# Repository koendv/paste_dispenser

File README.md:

# Solder Paste Dispenser

This is a solder paste dispenser. The controller supports unipolar and bipolar stepper motors, a foot pedal switch, an OLED display, a LED that blinks faster when the motor runs faster, and a menu system. The board has been designed with easy soldering in mind, using components size 0805 and up.

## Foot switch

Dispensing can be initiated either by pressing the *push* button on the dispenser, or by pushing down a foot pedal switch.

A foot pedal switch has the advantage that it frees up a hand. Using a foot switch is also more stable; pushing a button on the solder dispenser always moves the syringe tip a little bit.

Suitable foot pedals are [Adafruit product ID 423](https://www.adafruit.com/product/423) and [Sparkfun COM-11192](https://www.sparkfun.com/products/11192), and their equivalents at ebay and aliexpress.

These foot pedal switches are simple on/off switches, normally open. Speed controller foot pedals with a potentiometer will **not** work.

## Display

The display shows the motor speed.

The OLED display is a generic OLED module 0.91" diagonal, 128x32 pixel, I2C, SSD1306, as found on ebay, aliexpress and [others](https://www.google.com/search?q=OLED+module+0.91%22+128x32+I2C+SSD1306+price). Before buying, check the module has a 4-pin connection - GND, VCC, SDA, SCK - and uses a SSD1306 controller. The display *ought* not to touch any of the components below, but you can always put a bit of Kaptan tape on the back of the display, just to make sure.

The OLED display is optional. If you choose not to install the OLED display you can still check stepper speed on the serial console.

## Menu

There is a settings menu on the serial port. The serial port runs at 115200, 8N1, no flow control. Access the menu using a vt100 ansi terminal emulation, e.g. [PuTTY](https://putty.org/) on Windows, or *minicom* on Linux. On Android, use an USB OTG adapter and *Serial USB Terminal*. The settings menu allows you to configure forward speed, backward speed, pullback, and microstepping, and to store and recall these settings from non-volatile memory. The menu looks like this:

	[f] Forward speed 125 steps/sec
	[s] Forward steps 0 steps
	[b] Backward speed 500 steps/sec
	[d] Pullback delay 2000 millisec
	[p] Pullback steps 0 steps
	[m] Microstepping 2
	[n] Profile number 0
	[r] Restore profile
	[w] Save profile
	[h] Help

### Speed
Forward speed can be set using the *faster*/*slower* buttons on the dispenser itself or using the console menu.

If *forward steps* is zero, the syringe plunger is pushed down as long as you press the *push* button or the foot switch pedal. This is useful for making beads, and the normal setting when dispensing solder paste. If *forward steps* is non-zero, pushing the *forward* button or the foot switch moves the plunger down exactly the number of steps in the settings. This is useful for making precise, repeatable dots, e.g. as a glue or lubricating oil dispenser.

Backward speed can only be set using the console menu.

### Pullback
Sometimes liquid keeps oozing out after you stop dispensing. If *pullback steps* is non-zero, then after a *pullback delay* period of inactivity the plunger will move back *pullback steps*, to stop liquid oozing out. How successful this is and how many steps the plunger needs to pull back to stop the oozing depends upon the viscosity of the liquid. *Pullback* works better with low viscosity liquids than with high viscosity paste. Pullback is interesting if you use this as a dispenser for e.g. cyanoacrylate glue.

### Microstepping
The controller supports up to 1/64 microstepping. This is open loop voltage control microstepping.
Choose speed and microstepping that goes well with your stepper motor. This may take a bit of trial and error. Default is half-stepping, suitable for 28BYJ-48 steppers .

### Saved Profiles

Once you have found a setting that works, you can save it for later. Up to five profiles can be saved. These profiles are remembered even when the power is turned off. After power-up the last saved settings are used.

## Power supply

If you want to play it safe, use a 5.0V 1A phone charger as power supply. The TB6612 stepper motor driver IC supports 5V 1.2A continuous, but can be damaged by higher currents. Using a power supply with a maximum current less than 1.2A protects the driver IC in case of short circuit or stall.

The voltage range is 4.5V to 5.5V. More than 5.5V is too much for the atmega328p microcontroller; less than 4.5V and the TB6612 stepper driver stops working.

The board has a MOSFET for reverse polarity protection.

## Connecting everything

The controller board has four headers:

* J1 is the ISP connector for downloading the initial firmware to the atmega microcontroller.
* J2 connects to an USB to serial adapter (pins +5V, RX, TX, GND) and the footswitch (pins FTSW, GND). The footswitch is optional, but very handy.
* J3 is the connector for the stepper motor. Both unipolar and bipolar steppers can be connected. Connect one coil to pins A1 and A2, and one coil to pins B1 and B2. Connect the center tap of unipolar steppers to pin GND.
* J4 is the connector for the optional OLED display. Solder a 4-position female Dupont housing here.

## Bootstrapping

The first compile is the hardest.

Open the Arduino IDE. Compile the *paste dispenser* sketch, with these settings:

* Board: Arduino Pro or Pro Mini,
* Processor: Atmega328P (5V, 16MHz).

Generate an Intel Hex file with _Sketch -> Export Compiled Binary_. This creates two .hex files in the project directory, `arduino.ino.eightanaloginputs.hex` and `arduino.ino.with_bootloader.eightanaloginputs.hex`. The hex file we need is the one with the bootloader.
The ISP programmer is an arduino with the same logic levels as the target system. As the solder paste dispenser uses 5V logic, we need an Arduino with 5V logic levels as ISP programmer. Connect a 5V Arduino, e.g. an Arduino Uno, to your system. Compile and upload the _File -> Examples -> ArduinoISP_ sketch to the Uno. Connect the Arduino Uno to the solder paste dispenser board as follows:

Signal|Uno    |ISP pin
------|-------|--------
RST	|Uno pin 10|5
MOSI|Uno pin 11|4
MISO|Uno pin 12|1
SCK|Uno pin 13|3
VCC|Uno 5V|2
GND|Uno GND|6

Find `avrdude` in your Arduino IDE directories, change to the appropriate directory and do the following incantation:

	koen@raspberrypi:/opt/arduino-1.8.9/hardware/tools/avr $ ./bin/avrdude -C ./etc/avrdude.conf -p m328p -P /dev/ttyACM0 -c avrisp -b 19200 -U flash:w:/home/koen/src/paste_injector/arduino/arduino.ino.with_bootloader.eightanaloginputs.hex

where `/dev/ttyACM0` is the usb port of your Arduino Uno. Flashing should take about 20 seconds, and ends with "`xxx bytes of flash verified`" and "`Fuses OK`".

Set the fuses of the atmega328p for an external resonator at 16MHz:

	koen@raspberrypi:/opt/arduino-1.8.9/hardware/tools/avr $ ./bin/avrdude -C ./etc/avrdude.conf -c avrisp -p m328p -P /dev/ttyACM0 -b 19200  -U lfuse:w:0xff:m -U hfuse:w:0xda:m -U efuse:w:0xfd:m

The avrdude output ought to say: ```avrdude: safemode: Fuses OK (E:FD, H:DA, L:FF)```

If you just want to read the fuses:

	koen@raspberrypi:/opt/arduino-1.8.9/hardware/tools/avr $  ./bin/avrdude -C ./etc/avrdude.conf -c avrisp -p m328p -P /dev/ttyACM0 -b 19200 -U lfuse:r:-:i -v

This finishes writing bootloader and sketch to the solder paste dispenser. Disconnect the Arduino Uno. The atmega328p now contains a bootloader. Sketches can now be uploaded using the solder paste dispenser serial port.

## Firmware

The solder paste dispenser is an arduino system. Once the bootstrap loader has been installed the solder paste dispenser can be programmed using the arduino IDE.

To avoids spurious resets when connecting to the serial port, there is no capacitor between DTR and reset. But this also means that if you want to develop firmware for this board there is no automatic reset before uploading. Three options:

* Upload firmware using the ISP connector. This has to be done at least once, to upload the bootloader.
* Use the serial port to upload. This is what I usually do. Before uploading connect RST and ground with a Dupont jumper wire. RST and ground are next to each other on the ISP connector. In the Arduino IDE, click Sketch -> Upload, count to three and remove the jumper wire.
* When developing connect a 100n capacitor between serial adapter DTR and ISP connector RST pin. This allows the IDE to reset the microcontroller automatically just before uploading using the serial port.

## Soldering your own

The github contains arduino source and kicad pcb design files. You'll find the [schematic](https://github.com/koendv/paste_dispenser/raw/master/kicad/paste_dispenser/paste_dispenser_schematic.pdf), the [board layout](https://github.com/koendv/paste_dispenser/raw/master/kicad/paste_dispenser/paste_dispenser_board.pdf), and the [bill of materials](https://github.com/koendv/paste_dispenser/blob/master/kicad/paste_dispenser/paste_dispenser.csv). This is a link to the pcb as an orderable [shared project at oshpark](http://www.oshpark.com/shared_projects/V5txbi41), and these are the components as a [shared project at Mouser](https://www.mouser.com/ProjectManager/ProjectDetail.aspx?AccessID=61ff8d7d43). Here are [zipped gerbers](https://github.com/koendv/paste_dispenser/raw/master/kicad/paste_dispenser/gerbers.zip) for pcb manufacturing at [jlcpcb](https://jlcpcb.com/).

If you prefer not to solder SMD's you can also build the controller on a breadboard or as a through-hole pcb, as in this [fritzing sketch](https://github.com/koendv/paste_dispenser/raw/master/fritzing/paste_dispenser_fritzing_breadboard.pdf) of a 5V 16MHz Arduino Pro Mini and a TB6612 breakout module.

## Printing your own

Leave part orientation as is when imported into PrusaSlicer. Designed to print without support.

The [openscad/](https://github.com/koendv/paste_dispenser/tree/master/openscad) directory contains the .stl files for [3d-printing](https://www.treatstock.com/c/seaside-3d) the mechanical part of the solder paste dispenser in ABS using FDM. These parts need finishing as follows:

* Take the workpiece [insert_practice](https://github.com/koendv/paste_dispenser/blob/master/openscad/aerzetix-C19143/insert_practice.stl) and place 4 heat-set inserts, as a test. Set your soldering iron to the filament extrusion temperature used during 3D printing, about 255&deg;C.
* Take the workpiece [motor_mount](https://github.com/koendv/paste_dispenser/blob/master/openscad/aerzetix-C19143/motor_mount.stl) and place 4 heat-set inserts.
* Take the workpiece [plunger](https://github.com/koendv/paste_dispenser/blob/master/openscad/aerzetix-C19143/plunger.stl) and place 1 heat-set insert.
* Using **a drop** of acetone, glue the small conical [plunger tip](https://github.com/koendv/paste_dispenser/blob/master/openscad/aerzetix-C19143/plunger_tip.stl) to the plunger. Acetone is a solvent for ABS.

Mechanical assembly is next.
## Assembly

The mechanical part consists of stepper motor, coupler and leadscrew. 

The stepper motor is a [28BYJ-48](https://www.adafruit.com/product/858). The motor can be used "as is", or [modified to bipolar](https://coeleveld.com/wp-content/uploads/2016/10/Modifying-a-28BYJ-48-step-motor-from-unipolar-to-bipolar.pdf) for additional torque.

The leadscrew is 64mm of M4 threaded rod, 0.7mm pitch. The leadscrew mates with the M4 threaded insert in the plunger.

The coupler between motor and leadscrew is an [Aluminum 4mm to 5mm shaft couplers](https://www.google.com/search?&q=%2B%22D19*L25%22+Shaft+Coupling+Aluminium+flexible+%2B%224x5%22+aliexpress), readily available from ebay or aliexpress. The all-metal construction easily handles the torque.

Attach the stepper motor to the motor mount using two nylon or stainless steel M4x10 hex socket screws. Nylon screws keep the weight down. Attach the [syringe holder](https://github.com/koendv/paste_dispenser/blob/master/openscad/aerzetix-C19143/syringe_holder.stl) to the motor block with two M4x10 hex socket screws.

The syringe used is a BD 10cc "Luer-Lok", or one of its many [oriental clones](https://www.google.com/search?q=10cc+syringe+smt+smd+site%3A.aliexpress.com). Remove the black rubber piston head from the syringe and put it on the solder paste dispenser plunger.

Friction between rubber piston and syringe is what keeps the plunger from spinning. If during operation the plunger rotates instead of moving forward, clean the sides of the black rubber piston head with (isopropyl) alcohol to remove any grease. 

## Adding the Electronics

Align the pins of the PCB with the holes in the front of the motor mount. Fix the PCB in place with adhesive Velcro tape. Plug the OLED display in the connector marked "SDA SCK VCC GND". Connect the stepper motor to header J3.

Run 1-2m of cable from the 6-pin Dupont connector on the right of the PCB. The cable connects solder paste dispenser to a [5V TTL serial to USB converter](https://www.google.com/search?q=CH340C+site%3A.aliexpress.com) (pins +5V,RX,TX,GND) and the foot switch (pins FTSW, GND). 

If the motor turns the wrong way, swap pins A1 and A2, or pins B1 and B2.

At this point you have a working solder paste dispenser, ready for use.

## Practice makes perfect

For practice fill a syringe with a small amount (approx. 1 ml) of toothpaste. Print a pcb at scale 1:1 in black and white on paper and practice depositing toothpaste until you are comfortable with the solder paste dispenser.

Before filling the syringe, run a nylon wire inside the syringe body. A small piece of fishing line is suitable. This nylon wire creates a small leak in the seal between plunger and syringe body, allowing the air to escape while you push the plunger down. Once the plunger is down, simply pull the nylon wire out and you can begin dispensing.

## Notes

* There are a few situations which may result in breakage.
If the piston pushes against the bottom of an empty syringe, something has to give.
Likewise, if you try to squeeze paste out of a stoppered syringe.
In general, avoid "unstoppable force meets inmovable object" situations. Something will break - the motor may tear itself off its mounts, for instance.

* When not in use, loosen the syringe holder screws so the syringe isn't under constant pressure.

* A solder paste dispenser is a small motor which pushes the plunger of a syringe. You can use it for solder paste or solder flux, but the dispenser can also be used as a syringe pump, to create small dots of glue in a precise and repeatable way, or to put small drops of lubricating oil on a mechanism.

* The controller is not restricted to any specific model of solder paste dispenser; if a syringe pump uses a 5- or 6-wire unipolar or a 4-wire bipolar stepper motor, there's a reasonable chance this will work. Just check the stepper works at 5V and current stays below 1.2 amps.

* FDM print settings: Increase perimeters on the pieces with heat-set inserts ([motor_mount](https://github.com/koendv/paste_dispenser/blob/master/openscad/aerzetix-C19143/motor_mount.stl) and [plunger](https://github.com/koendv/paste_dispenser/blob/master/openscad/aerzetix-C19143/plunger.stl)); this gives the heat-set inserts more material to grip onto. 

* Exactly how hard do we need to push? Take a syringe and (kitchen) scales. Grab the syringe by the syringe body, and push the syringe piston against the scales until the syringe releases solder paste. Take note of the weight the scales indicate. If the scales indicates pounds, multiply by 5 to get Newtons. If the scales indicate kilogrammes, multiply by 10 to get Newtons.
Measured this way, pushing the plunger of 5cc and 10cc syringes of solder flux and solder paste needs a force between 20N and 30N.

* The kicad pcb hardware design is under Creative Commons - Attribution Share Alike license.

* This design was inspired by solder paste dispensers by [zapta](https://www.thingiverse.com/thing:1119914) and [geir](https://www.thingiverse.com/thing:384680). The mechanical part is a remix of zapta's, with only minor changes.

* This design was built around a Atmega328p "Pro Mini" and a TB6612 stepper driver. An alternative design would be a STM32F103 "Black Pill" and a TMC2130 SilentStepStick stepper driver. The STM32F103 has enough cpu to run a comprehensive menu system and built-in usb. The TMC2130 stall detection allows detecting when the plunger has reached the bottom of the syringe, so software can move the plunger back a few steps before any mechanical damage occurs. But such a design would hit a different price point.

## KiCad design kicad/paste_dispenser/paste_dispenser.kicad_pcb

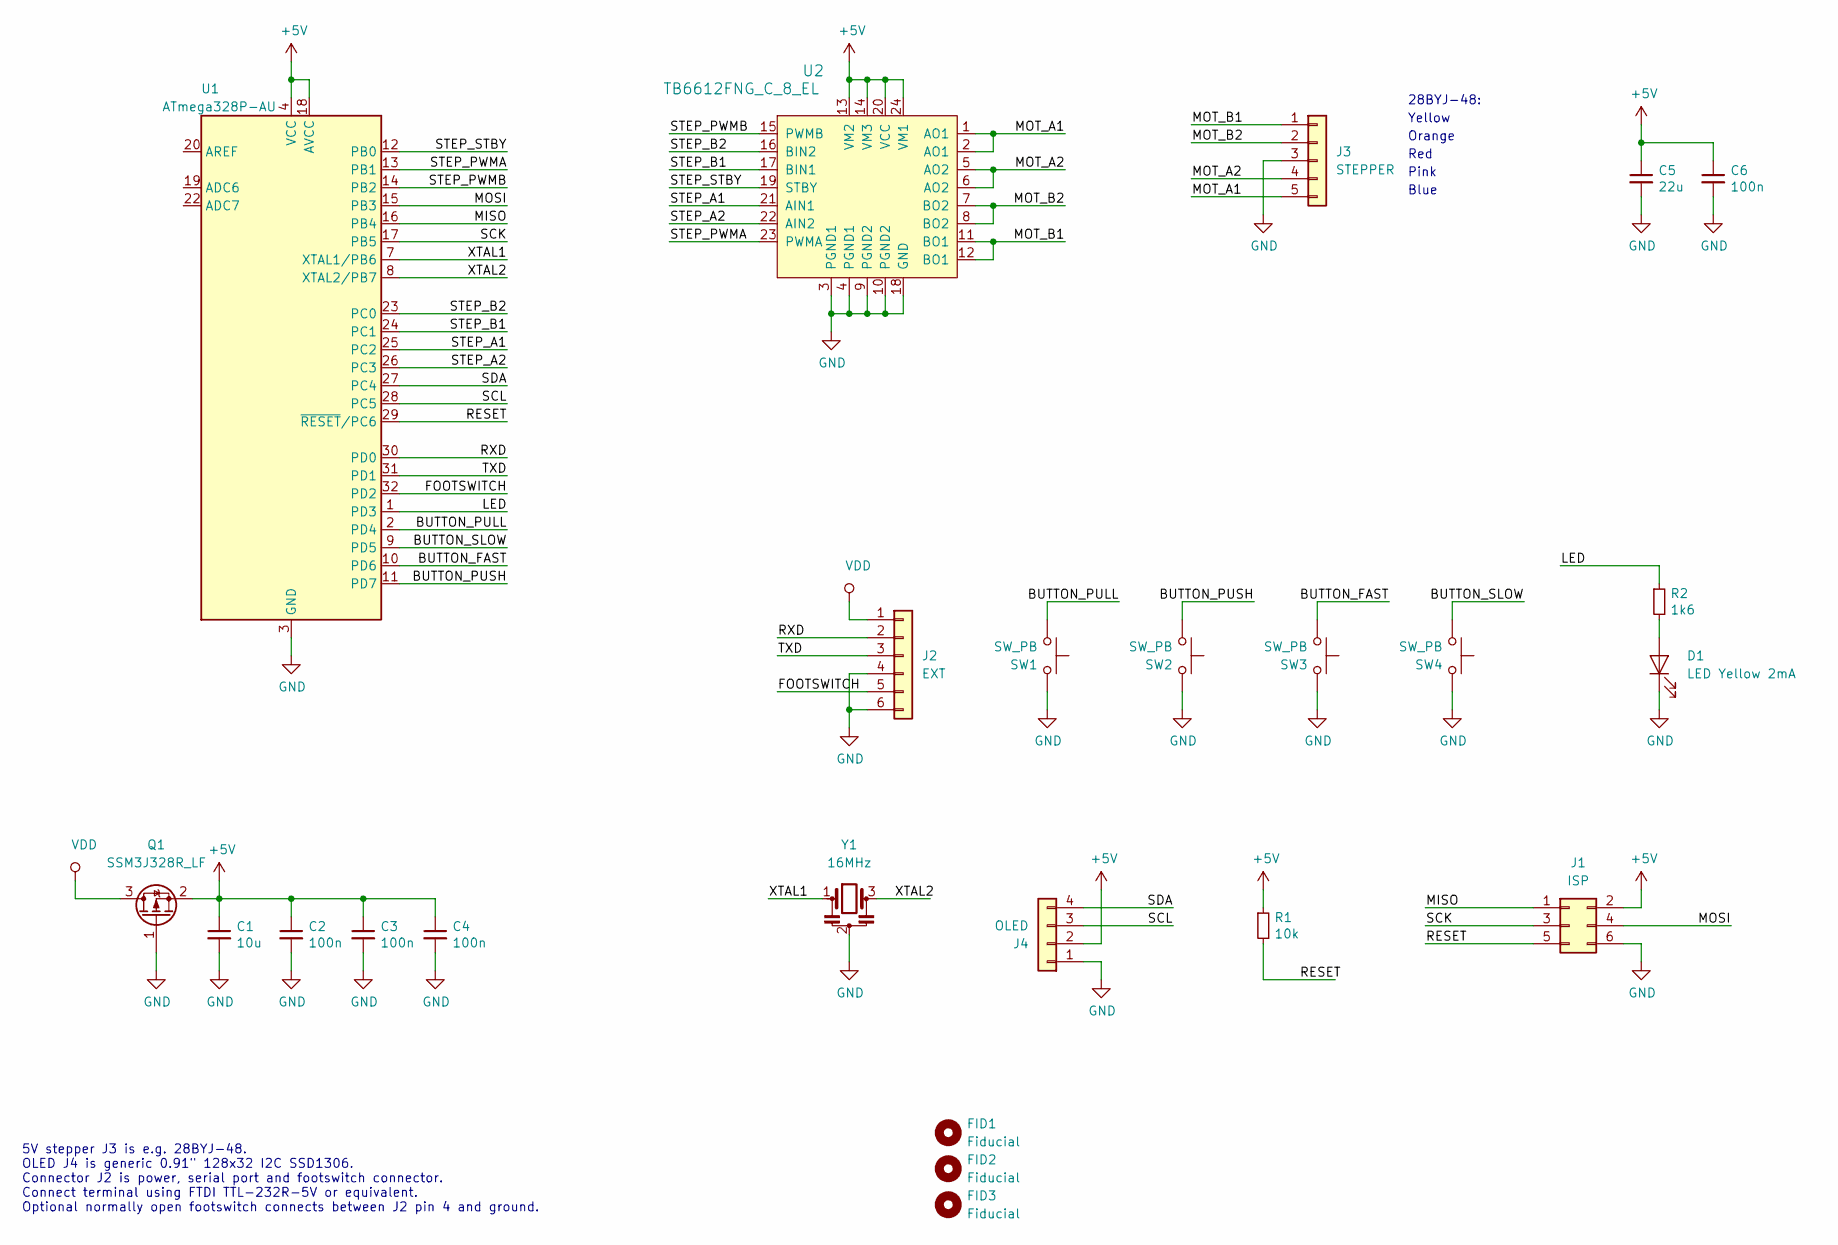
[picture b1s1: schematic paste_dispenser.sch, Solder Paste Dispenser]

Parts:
C1: 10u; C_0805_2012Metric; Manufacturer Part No CC805KKX5R7BB106
C2, C3, C4, C6: 100n; C_0805_2012Metric; Manufacturer Part No CC805KRX7R7BB104
C5: 22u; C_1206_3216Metric; Manufacturer Part No EMK316BB7226ML-T
D1: LED Yellow 2mA; LED_0805_2012Metric; Manufacturer Part No APTD2012LSYCK
FID1, FID2, FID3: Fiducial; Fiducial_1mm_Dia_2.54mm_Outer_CopperTop
J1: ISP; PinHeader_2x03_P2.54mm_Vertical; Manufacturer Part No 2822
J2: EXT; PinHeader_1x06_P2.54mm_Vertical; Manufacturer Part No 70553-0005
J3: STEPPER; PinHeader_1x05_P2.54mm_Vertical; Manufacturer Part No DNP
J4: OLED; PinSocket_1x04_P2.54mm_Vertical; Manufacturer Part No M20-7820442
Q1: SSM3J328R_LF; SOT-23; Manufacturer Part No SSM3J328R,LF
R1: 10k; R_0805_2012Metric; Manufacturer Part No AC0805FR-0710KL
R2: 1k6; R_0805_2012Metric; Manufacturer Part No AC0805FR-071K6L
SW1, SW2, SW3, SW4: SW_PB; SW_PUSH_6mm; Manufacturer Part No B3F-1000
U1: ATmega328P-AU; TQFP-32_7x7mm_P0.8mm; Manufacturer Part No ATMEGA328P-AU
U2: TB6612FNG_C_8_EL; LSSOP-24_W5.6mm; Manufacturer Part No TB6612FNG,C,8,EL
Y1: 16MHz; Resonator_SMD_muRata_CSTxExxV-3Pin_3.0x1.1mm_HandSoldering; Manufacturer Part No CSTNE16M0V530000R

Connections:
+5V: C1.1, C2.1, C3.1, C4.1, C5.1, C6.1, J1.2, J4.2, Q1.2 (S), R1.1, U1.4 (VCC), U1.6 (VCC), U1.18 (AVCC), U2.13 (VM2), U2.14 (VM3), U2.20 (VCC), U2.24 (VM1)
/BUTTON_FAST: SW3.1, U1.10 (PD6)
/BUTTON_PULL: SW1.1, U1.2 (PD4)
/BUTTON_PUSH: SW2.1, U1.11 (PD7)
/BUTTON_SLOW: SW4.1, U1.9 (PD5)
/FOOTSWITCH: J2.5, U1.32 (PD2)
/LED: R2.1, U1.1 (PD3)
/MISO: J1.1, U1.16 (PB4)
/MOSI: J1.4, U1.15 (PB3)
/MOT_A1: J3.5, U2.1 (AO1), U2.2 (AO1)
/MOT_A2: J3.4, U2.5 (AO2), U2.6 (AO2)
/MOT_B1: J3.1, U2.11 (BO1), U2.12 (BO1)
/MOT_B2: J3.2, U2.7 (BO2), U2.8 (BO2)
/RESET: J1.5, R1.2, U1.29 (~RESET~/PC6)
/RXD: J2.2, U1.30 (PD0)
/SCK: J1.3, U1.17 (PB5)
/SCL: J4.3, U1.28 (PC5)
/SDA: J4.4, U1.27 (PC4)
/STEP_A1: U1.25 (PC2), U2.21 (AIN1)
/STEP_A2: U1.26 (PC3), U2.22 (AIN2)
/STEP_B1: U1.24 (PC1), U2.17 (BIN1)
/STEP_B2: U1.23 (PC0), U2.16 (BIN2)
/STEP_PWMA: U1.13 (PB1), U2.23 (PWMA)
/STEP_PWMB: U1.14 (PB2), U2.15 (PWMB)
/STEP_STBY: U1.12 (PB0), U2.19 (STBY)
/TXD: J2.3, U1.31 (PD1)
/XTAL1: U1.7 (XTAL1/PB6), Y1.1
/XTAL2: U1.8 (XTAL2/PB7), Y1.3
GND: C1.2, C2.2, C3.2, C4.2, C5.2, C6.2, D1.1 (K), J1.6, J2.4, J2.6, J3.3, J4.1, Q1.1 (G), SW1.2, SW2.2, SW3.2, SW4.2, U1.3 (GND), U1.5 (GND), U1.21 (GND), U2.3 (PGND1), U2.4 (PGND1), U2.9 (PGND2), U2.10 (PGND2), U2.18 (GND), Y1.2
unnamed: D1.2 (A), R2.2
VDD: J2.1, Q1.3 (D)

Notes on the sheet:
5V stepper J3 is e.g. 28BYJ-48. OLED J4 is generic 0.91" 128x32 I2C SSD1306. Connector J2 is power, serial port and footswitch connector. Connect terminal using FTDI TTL-232R-5V or equivalent. Optional normally open footswitch connects between J2 pin 4 and ground.
Yellow
Orange
Red
Pink
Blue
28BYJ-48:

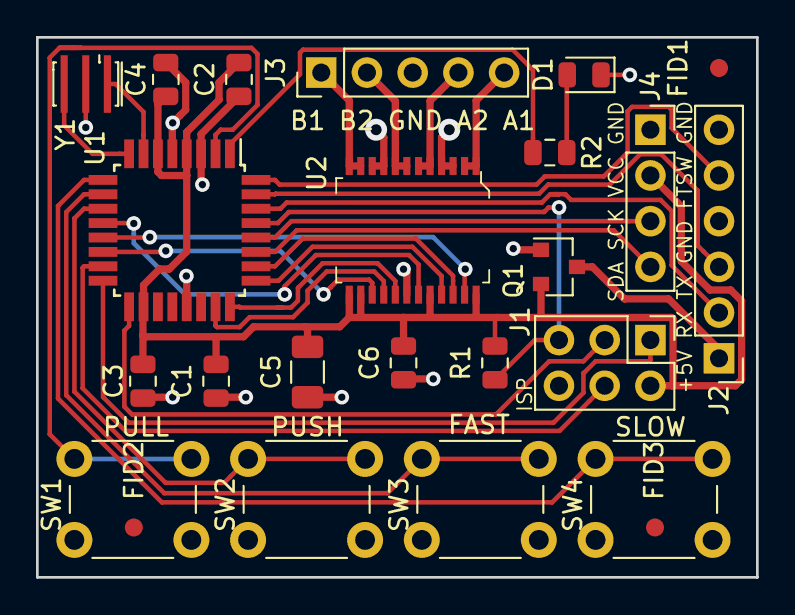
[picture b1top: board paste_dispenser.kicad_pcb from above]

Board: 2 copper layers, 40.0 x 30.0 mm, 24 parts (0 on the bottom side), 31 nets.

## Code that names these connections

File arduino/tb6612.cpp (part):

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
  // bitmasks for the stepper wires.
  
  static const uint8_t AIN1 = (1 << 2); // Coil A+ corresponds to port C bit 2. (PC2)
  static const uint8_t AIN2 = (1 << 3); // Coil A- corresponds to port C bit 3. (PC3)
  static const uint8_t BIN1 = (1 << 1); // Coil B+ corresponds to port C bit 1. (PC1)
  static const uint8_t BIN2 = (1 << 0); // Coil B- corresponds to port C bit 0. (PC0)
  
  static const uint8_t kAllPins = AIN1 | AIN2 | BIN1 | BIN2; // mask for all stepper wires.
  
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
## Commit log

2019-06-30 release
2019-06-30 add links
2019-07-07 add bom
2019-07-07 add header
2019-07-07 foot pedal switch
2019-07-08 serial console
2019-07-09 microstepping
2019-07-09 notes
2019-07-11 gerbers
2019-07-11 jlcpcb
2019-07-11 assembly
2019-07-12 wakeup fix
2019-07-12 help text 80col
2019-07-13 optimisation
2019-07-13 range check
2019-07-13 typo
2019-07-14 default speed
2019-07-14 firmware
2019-07-15 led blink rate
2019-07-15 led blink
2019-07-18 autodetect i2c
2019-07-27 mechanical
2019-07-27 chamfer
2019-08-09 cleanup
2019-08-09 remix
2019-08-09 mods doc
2019-08-13 threaded knurled brass inserts
2019-08-14 threaded knurled tapered brass inserts
2019-08-27 ide 1.8.9
2019-08-29 microstep init
2019-09-01 picture
2019-09-03 add right-angle dupont
2019-09-14 tweak for Prusa
2019-09-14 add pcb
2019-09-15 coupler
2019-09-15 new build
2019-09-15 naming
2019-09-21 coupler redesign
2019-09-21 new coupler
2019-09-22 rm overhangs
2019-09-25 cover
2019-09-25 ready
2019-10-08 datasheet
2020-01-07 prusa
2020-01-29 fuses
2020-01-31 footswitch pic
2020-01-31 footswitch
2020-01-31 pic pcb
2020-02-01 pullback
2020-02-16 fix dia

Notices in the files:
kicad/paste_dispenser/paste_dispenser.kicad_pcb:
Released under the Creative Commons Attribution-ShareAlike 4.0 license.
